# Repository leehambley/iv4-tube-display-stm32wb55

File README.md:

# iv4-tube-display-stm32wb55

### Images

rendered with [kicad-render](https://github.com/linalinn/kicad-render)

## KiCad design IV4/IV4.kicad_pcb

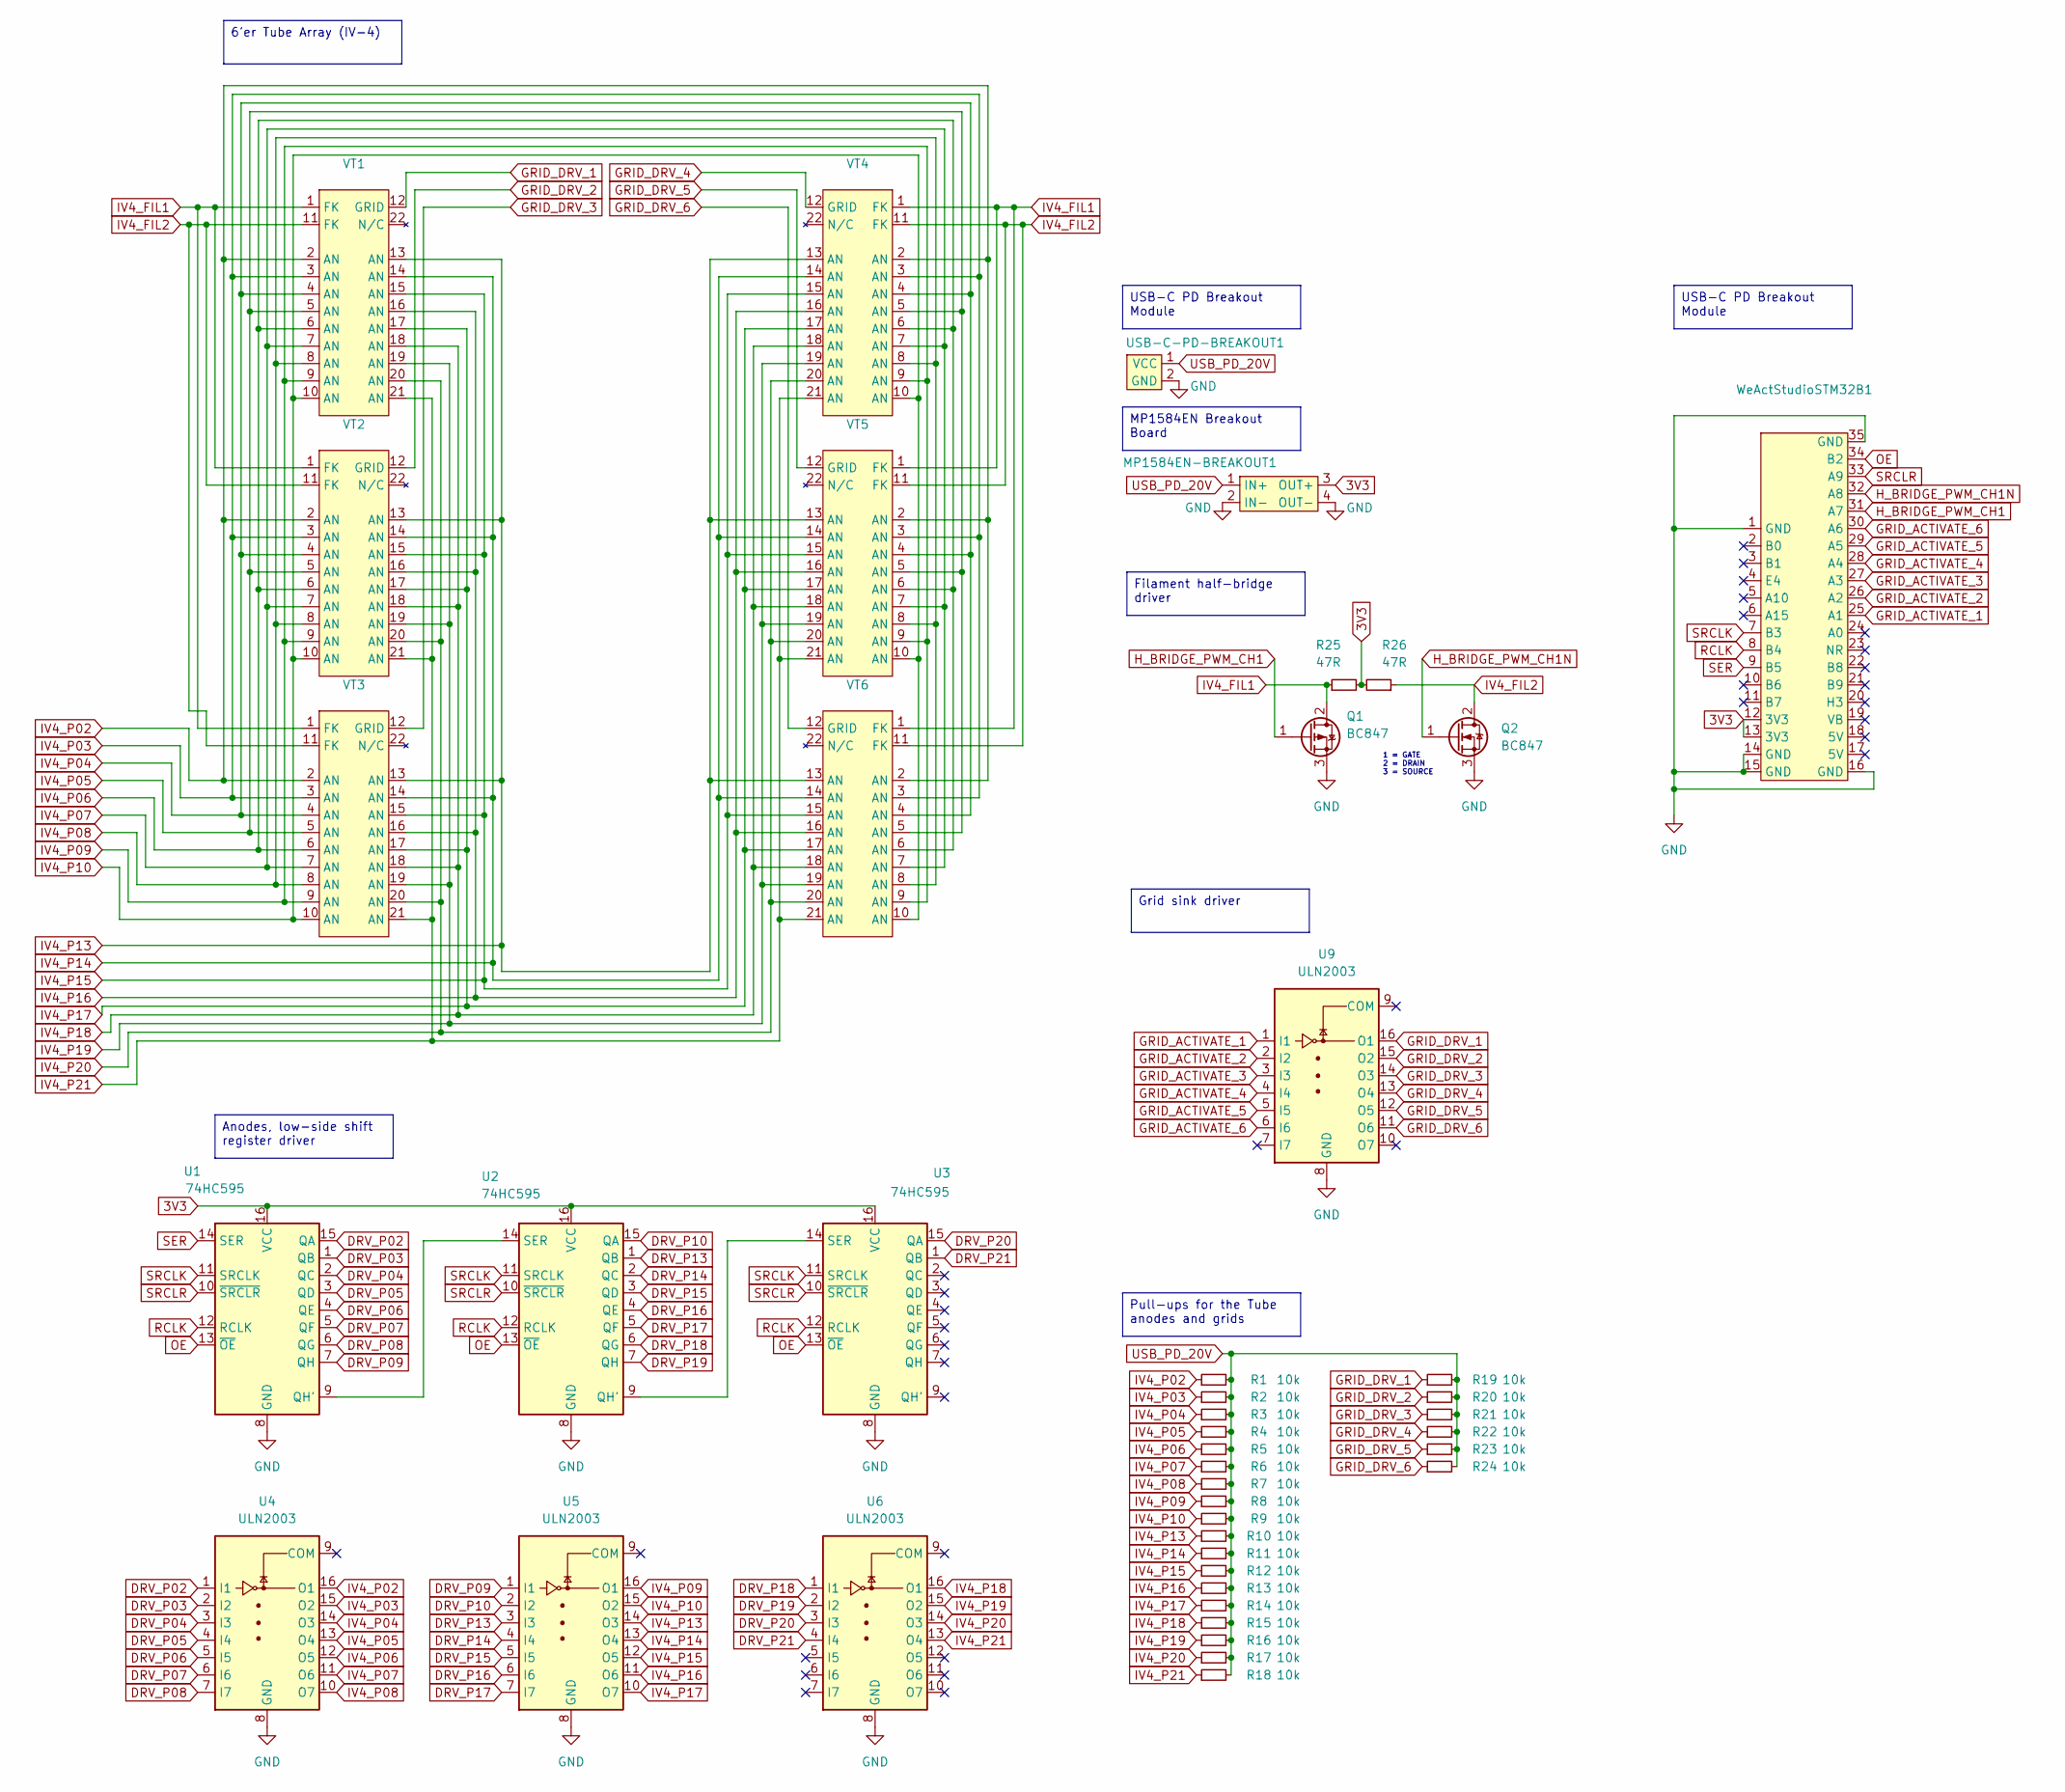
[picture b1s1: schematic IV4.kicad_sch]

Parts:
MP1584EN-BREAKOUT1: Untitled_1
Q1, Q2: BC847; TSOT-23
R1, R2, R3, R4, R5, R6, R7, R8, R9, R10, R11, R12, R13, R14, R15, R16, R17, R18, R19, R20, R21, R22, R23, R24: 10k; R_0402_1005Metric
R25, R26: 47R; R_0402_1005Metric
U1, U2, U3: 74HC595; SOIC-16_3.9x9.9mm_P1.27mm
U4, U5, U6, U9: ULN2003; SOIC-16_3.9x9.9mm_P1.27mm
USB-C-PD-BREAKOUT1: ARCELI USB-C PD Breakout
VT1, VT2, VT3, VT4, VT5, VT6: IV4
WeActStudioSTM32B1: WeActStudioSTM32WB55

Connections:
3V3: MP1584EN-BREAKOUT1.3 (OUT+), R25.2, R26.2, U1.16 (VCC), U2.16 (VCC), U3.16 (VCC), WeActStudioSTM32B1.12 (3V3), WeActStudioSTM32B1.13 (3V3)
DRV_P02: U1.15 (QA), U4.1 (I1)
DRV_P03: U1.1 (QB), U4.2 (I2)
DRV_P04: U1.2 (QC), U4.3 (I3)
DRV_P05: U1.3 (QD), U4.4 (I4)
DRV_P06: U1.4 (QE), U4.5 (I5)
DRV_P07: U1.5 (QF), U4.6 (I6)
DRV_P08: U1.6 (QG), U4.7 (I7)
DRV_P09: U1.7 (QH), U5.1 (I1)
DRV_P10: U2.15 (QA), U5.2 (I2)
DRV_P13: U2.1 (QB), U5.3 (I3)
DRV_P14: U2.2 (QC), U5.4 (I4)
DRV_P15: U2.3 (QD), U5.5 (I5)
DRV_P16: U2.4 (QE), U5.6 (I6)
DRV_P17: U2.5 (QF), U5.7 (I7)
DRV_P18: U2.6 (QG), U6.1 (I1)
DRV_P19: U2.7 (QH), U6.2 (I2)
DRV_P20: U3.15 (QA), U6.3 (I3)
DRV_P21: U3.1 (QB), U6.4 (I4)
GND: MP1584EN-BREAKOUT1.2 (IN-), MP1584EN-BREAKOUT1.4 (OUT-), Q1.3 (S), Q2.3 (S), U1.8 (GND), U2.8 (GND), U3.8 (GND), U4.8 (GND), U5.8 (GND), U6.8 (GND), U9.8 (GND), USB-C-PD-BREAKOUT1.2 (GND), WeActStudioSTM32B1.1 (GND), WeActStudioSTM32B1.14 (GND), WeActStudioSTM32B1.15 (GND), WeActStudioSTM32B1.16 (GND), WeActStudioSTM32B1.35 (GND)
GRID_ACTIVATE_1: U9.1 (I1), WeActStudioSTM32B1.25 (A1)
GRID_ACTIVATE_2: U9.2 (I2), WeActStudioSTM32B1.26 (A2)
GRID_ACTIVATE_3: U9.3 (I3), WeActStudioSTM32B1.27 (A3)
GRID_ACTIVATE_4: U9.4 (I4), WeActStudioSTM32B1.28 (A4)
GRID_ACTIVATE_5: U9.5 (I5), WeActStudioSTM32B1.29 (A5)
GRID_ACTIVATE_6: U9.6 (I6), WeActStudioSTM32B1.30 (A6)
GRID_DRV_1: R19.1, U9.16 (O1), VT1.12 (GRID)
GRID_DRV_2: R20.1, U9.15 (O2), VT2.12 (GRID)
GRID_DRV_3: R21.1, U9.14 (O3), VT3.12 (GRID)
GRID_DRV_4: R22.1, U9.13 (O4), VT4.12 (GRID)
GRID_DRV_5: R23.1, U9.12 (O5), VT5.12 (GRID)
GRID_DRV_6: R24.1, U9.11 (O6), VT6.12 (GRID)
H_BRIDGE_PWM_CH1: Q1.1 (G), WeActStudioSTM32B1.31 (A7)
H_BRIDGE_PWM_CH1N: Q2.1 (G), WeActStudioSTM32B1.32 (A8)
IV4_FIL1: Q1.2 (D), R25.1, VT1.1 (FK), VT2.1 (FK), VT3.1 (FK), VT4.1 (FK), VT5.1 (FK), VT6.1 (FK)
IV4_FIL2: Q2.2 (D), R26.1, VT1.11 (FK), VT2.11 (FK), VT3.11 (FK), VT4.11 (FK), VT5.11 (FK), VT6.11 (FK)
IV4_P02: R1.1, U4.16 (O1), VT1.2 (AN), VT2.2 (AN), VT3.2 (AN), VT4.2 (AN), VT5.2 (AN), VT6.2 (AN)
IV4_P03: R2.1, U4.15 (O2), VT1.3 (AN), VT2.3 (AN), VT3.3 (AN), VT4.3 (AN), VT5.3 (AN), VT6.3 (AN)
IV4_P04: R3.1, U4.14 (O3), VT1.4 (AN), VT2.4 (AN), VT3.4 (AN), VT4.4 (AN), VT5.4 (AN), VT6.4 (AN)
IV4_P05: R4.1, U4.13 (O4), VT1.5 (AN), VT2.5 (AN), VT3.5 (AN), VT4.5 (AN), VT5.5 (AN), VT6.5 (AN)
IV4_P06: R5.1, U4.12 (O5), VT1.6 (AN), VT2.6 (AN), VT3.6 (AN), VT4.6 (AN), VT5.6 (AN), VT6.6 (AN)
IV4_P07: R6.1, U4.11 (O6), VT1.7 (AN), VT2.7 (AN), VT3.7 (AN), VT4.7 (AN), VT5.7 (AN), VT6.7 (AN)
IV4_P08: R7.1, U4.10 (O7), VT1.8 (AN), VT2.8 (AN), VT3.8 (AN), VT4.8 (AN), VT5.8 (AN), VT6.8 (AN)
IV4_P09: R8.1, U5.16 (O1), VT1.9 (AN), VT2.9 (AN), VT3.9 (AN), VT4.9 (AN), VT5.9 (AN), VT6.9 (AN)
IV4_P10: R9.1, U5.15 (O2), VT1.10 (AN), VT2.10 (AN), VT3.10 (AN), VT4.10 (AN), VT5.10 (AN), VT6.10 (AN)
IV4_P13: R10.1, U5.14 (O3), VT1.13 (AN), VT2.13 (AN), VT3.13 (AN), VT4.13 (AN), VT5.13 (AN), VT6.13 (AN)
IV4_P14: R11.1, U5.13 (O4), VT1.14 (AN), VT2.14 (AN), VT3.14 (AN), VT4.14 (AN), VT5.14 (AN), VT6.14 (AN)
IV4_P15: R12.1, U5.12 (O5), VT1.15 (AN), VT2.15 (AN), VT3.15 (AN), VT4.15 (AN), VT5.15 (AN), VT6.15 (AN)
IV4_P16: R13.1, U5.11 (O6), VT1.16 (AN), VT2.16 (AN), VT3.16 (AN), VT4.16 (AN), VT5.16 (AN), VT6.16 (AN)
IV4_P17: R14.1, U5.10 (O7), VT1.17 (AN), VT2.17 (AN), VT3.17 (AN), VT4.17 (AN), VT5.17 (AN), VT6.17 (AN)
IV4_P18: R15.1, U6.16 (O1), VT1.18 (AN), VT2.18 (AN), VT3.18 (AN), VT4.18 (AN), VT5.18 (AN), VT6.18 (AN)
IV4_P19: R16.1, U6.15 (O2), VT1.19 (AN), VT2.19 (AN), VT3.19 (AN), VT4.19 (AN), VT5.19 (AN), VT6.19 (AN)
IV4_P20: R17.1, U6.14 (O3), VT1.20 (AN), VT2.20 (AN), VT3.20 (AN), VT4.20 (AN), VT5.20 (AN), VT6.20 (AN)
IV4_P21: R18.1, U6.13 (O4), VT1.21 (AN), VT2.21 (AN), VT3.21 (AN), VT4.21 (AN), VT5.21 (AN), VT6.21 (AN)
unnamed: U1.9 (QH'), U2.14 (SER)
unnamed: U2.9 (QH'), U3.14 (SER)
OE: U1.13 (~OE), U2.13 (~OE), U3.13 (~OE), WeActStudioSTM32B1.34 (B2)
RCLK: U1.12 (RCLK), U2.12 (RCLK), U3.12 (RCLK), WeActStudioSTM32B1.8 (B4)
SER: U1.14 (SER), WeActStudioSTM32B1.9 (B5)
SRCLK: U1.11 (SRCLK), U2.11 (SRCLK), U3.11 (SRCLK), WeActStudioSTM32B1.7 (B3)
SRCLR: U1.10 (~SRCLR), U2.10 (~SRCLR), U3.10 (~SRCLR), WeActStudioSTM32B1.33 (A9)
USB_PD_20V: MP1584EN-BREAKOUT1.1 (IN+), R1.2, R2.2, R3.2, R4.2, R5.2, R6.2, R7.2, R8.2, R9.2, R10.2, R11.2, R12.2, R13.2, R14.2, R15.2, R16.2, R17.2, R18.2, R19.2, R20.2, R21.2, R22.2, R23.2, R24.2, USB-C-PD-BREAKOUT1.1 (VCC)

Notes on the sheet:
1 = GATE 2 = DRAIN 3 = SOURCE
Anodes, low-side shift register driver
Grid sink driver
Filament half-bridge driver
MP1584EN Breakout Board
USB-C PD Breakout Module
Pull-ups for the Tube anodes and grids
6'er Tube Array (IV-4)

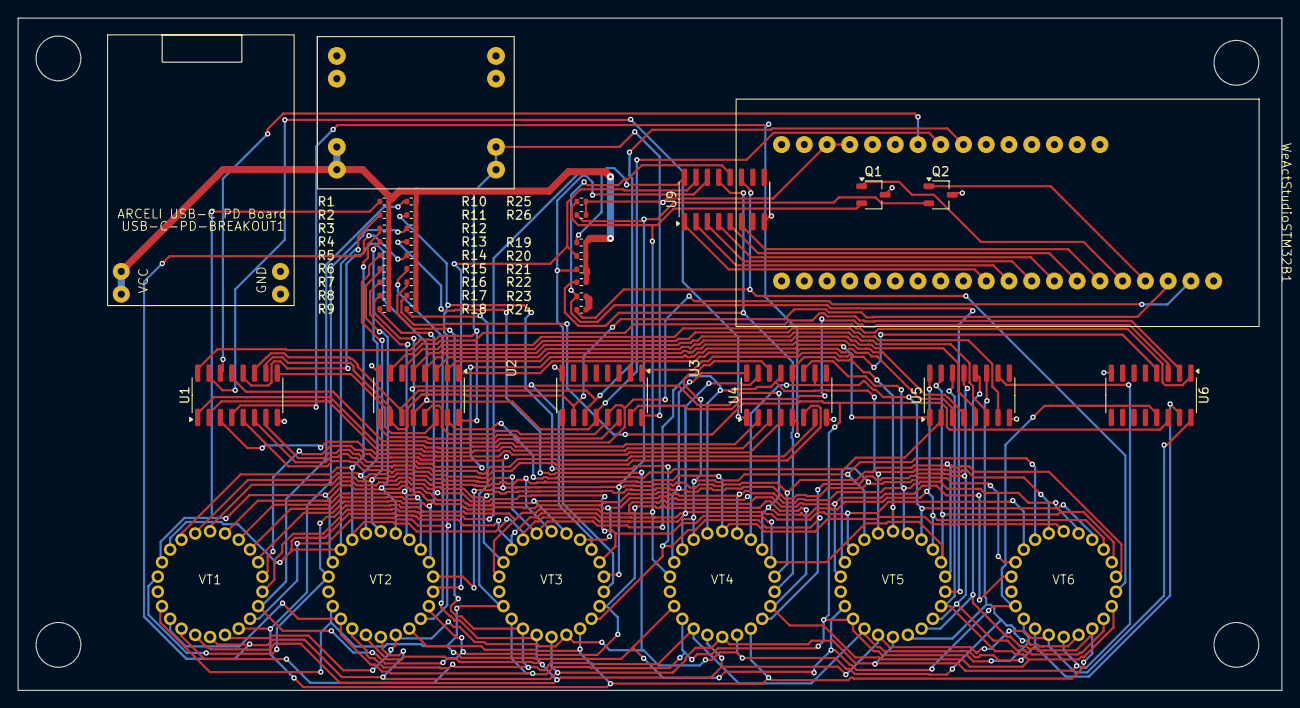
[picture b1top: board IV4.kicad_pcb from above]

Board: 2 copper layers, 141.1 x 75.1 mm, 44 parts (0 on the bottom side), 62 nets.

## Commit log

2025-04-20 add kicad render workflow
2025-04-20 fix path to .pcb
2025-04-20 try workflow dispatch
2025-04-20 fix path to images
